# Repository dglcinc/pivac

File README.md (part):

# pivac
Python package to pull data from Raspberry-Pi (RPi)-based inputs, and output JSON data. Supports the assembly and delivery of RPi-based monitoring and control solutions, like HVAC and home automation. Could also be used for other monitoring projects like home brewing and sous vide. These inputs include both RPi hardware inputs (like GPIO pins and GPIO-supported protocols like 1-Wire), as well as external sources useful for assembling a complete solution, such as HTTP-based data feeds and web sites (a.k.a. screen scraping.) This package is "input-only" - no provision is (currently) made to process updates.

Currently supported inputs include:

* **1-WireTherm**: 1-Wire-based Dallas temperature sensors (thermometers)
* **GPIO**: Generic reads of RPi GPIO pins, pulled high or low using internal pullup resistors
* **RedLink**: Screen scraping of Honeywell's website for RedLink thermostats, mytotalconnectcomfort.com (requires an account and installed RedLink equipment)
* **TED5000**: Parsing of the live XML feed from the TED5000 home energy monitoring solution
* **ArduinoSensor**: Pressure sensor data from an Arduino over HTTP (e.g. Fusch 100PSI, Fusch 200PSI) — a single implementation used by multiple config sections via the `module:` key
* **Emporia**: Per-circuit power readings in Watts from an Emporia Vue Gen 2 energy monitor, via the PyEmVue cloud API
* **Sentry**: Boiler operating data from an NTI Trinity Ti-200 boiler controller, read via computer vision from a Tapo C120 IP camera pointed at the Sentry 2100 display
* **FlirFX**: Temperature and humidity from a FLIR camera

The package is extensible, so if the supported inputs don't meet your needs, you can add your own.

The package provides each input individually, so you can pick and choose which ones you want. Customization is possible via a configuration file.

# Overview
This package has the modest aspiration of simplifying a certain class of monitoring (and eventually control) use cases for Raspberry Pi based projects, by providing pre-built recipes for acquiring data, and emitting the data in JSON format. It has no aspirations to replace more general RPi packages like GPIO and w1Therm (in fact it is built on top of them). Examples cases using JSON data:

* Delivering a status website on your RPi, available on your local network
* Modeling your RPi as an Amazon Web Services (AWS) IOT "thing", uploading your data as thing shadow "updates", and using AWS Lambdas to do stuff (store data, render static websites, etc.)
* Inputting data to a [Signal K](http://www.signalk.org) server running on your RPi, and leveraging the Signal K ecosystem to process and display your data
* Capturing a time series collection of the data in a database such as InfluxDB, and analyzing in a charting tool such as Grafana

## Standard call interface, Diverse inputs, JSON output
The core concept of this package is simple - go get some data from somewhere related to your use case (a piece of HVAC equipment or a home automation product website) and return it as a JSON-formatted data collection. You can then reformat it and deliver it in a number of different ways. A standard call interface and configuration file format makes it easy to add new modules for new input types.

## Why Python?
What can I say, I like Python. It's easy and fun to write some pretty fancy stuff. And supposedly it's [where the Pi in Raspberry Pi comes from](https://www.techspot.com/article/531-eben-upton-interview/) (Pi-thon, get it?).

## Why RPi and not Arduino
I actually started this project on Arduino, using a packaged Arduino-based PLC from [Digital Loggers](https://dlidirect.com/products/diy-programmable-controller). There are some advantages to using the Arduino in terms of analog inputs, PWM handling, performance, etc. and the DL PLC is pretty cool, with optical input isolators, open collector outputs, LCD screen, etc. I didn't really need these features, and the programming model was not fun (e.g. coding Lua on NodeMCU to do your Wi-Fi comms., serial-loading sketches constantly, etc.) Great if you need it, a pain if you don't. I abandoned this because the RPi is way simpler - I can SSH in headless, use a standard UNIX programming model and tools (which I know very well) code in fun languages like Python -- what's not to like? The code for the (archived) Arduino version is at [HVAC-plc](https://github.com/dglcinc/HVAC-plc).

Ambitious contributors/forkers who like the RPi model and also have more need for Arduino features could follow the suggestion in this [excellent Maker article](http://makezine.com/projects/tutorial-raspberry-pi-gpio-pins-and-python/) to piggy-back an Arduino to your RPi's serial port, and add a module that reads the Arduino and supplies JSON as output.

## Why polling of the GPIO pins, rather than events?
* It's simpler
* I want to store time series data without interpolating
* It makes it easy to disconnect and reconnect to your aggregator and still see the complete picture of current state

I suppose you could do some work to optimize by only generating output when state changes, but that gets a lot more complicated and I don't really see the benefit for my use case, so I didn't do it.

## Why not control too, not just monitoring?
Eventually. For the HVAC use case specifically, I have shied away from making the correct operation of the HVAC system dependent on the RPi:

* It means you can't condition your space if you have a problem with the RPi
* It's very hard to find HVAC technicians that can or will work on RPi-based controls

I'm pondering a design that allows some control or automation by the RPi, but fallback to full mechanical behavior if the RPi is down. When I have a good plan for that I'll reconsider having the RPi control the system.

## Suggestions for Processing the Output
My original project delivered the JSON from my data sources into a python script that dynamically generated a simple web page on the RPi as an Apache-based Python CGI. I then internet-enabled my project (to avoid doing port forwarding to my RPi, and to learn AWS IOT...) by setting up the RPi as a thing on Amazon's IOT service, and using a Lambda to generate an S3-based static page whenever the thing shadow is updated by my RPi, once every few seconds. I know kinda sloppy but it works... You could optimize your updating to minimize charges for Lambda, etc., but at the volume I consume (low and cheap) it's not a priority. The github repository for the archived version is at [HVAC-pi](https://github.com/dglcinc/HVAC-pi), including the python cgi in the /local subdirectory, and the AWS thing code in /hvac-pi-aws.

## Signal K!
I serendipitously stumbled on a project targeted at the boating community, [Signal K](http://www.signalk.org). Some features of that project are strikingly similar to mine (gather data from a variety of disparate sources and protocols and rationalize them into a JSON-based data stream). They have more and better developers, and a pretty highly evolved ecosystem. So I've converted to outputting my JSON to a Signal K server, and then using the tools in that ecosystem (such as the excellent iOS app [WilhelmSK](http://www.wilhelmsk.com)) to store and render my data. It's very cool. Check it out. Here are screenshots from the WilhelmSK iPhone and iPad app. The first screen is the real-time gauges to monitor all my vital statistics, and the second screen is a Grafana dashboard visualizing time series data for all the inputs, stored in an InfluxDB database.

# Architecture
The features of the architecture are:

* **Isolated Operation**: Doesn't impact operation of the HVAC equipment (no direct control, to avoid HVAC downtime due to RPI and sensor issues)
* **Real Time and Historical Data**: Displays status of all the equipment, stores and plots historical data automatically for all modules
* **Modular Sensor Inputs**: Modular sensor feeds so it can be adapted to different systems with minimal coding
* **User-Configurable Display**: Easily configurable user interface for personal preferences, mobile display works on-premise or remote

The data flow and component view of the architecture is as follows:

```mermaid
%%{init: {'flowchart': {'htmlLabels': true, 'curve': 'linear', 'subgraphTitleMargin': {'top': 30, 'bottom': 30}}, 'theme': 'base'}}%%
graph TD
    subgraph Devices["Physical Devices"]
        A1["Arduino<br/>10.0.0.114<br/>Hydronic PSI<br/>(Fusch 100 PSI)"]
        A2["Arduino<br/>10.0.0.219<br/>DHW PSI<br/>(Fusch 200 PSI)"]
        CAM["Tapo C120<br/>10.0.0.19<br/>RTSP 2560×1440"]
        OW["1-Wire Sensors<br/>GPIO (temp)"]
        GPIO["GPIO Pins<br/>Switches / Relays"]
        RL["Honeywell<br/>mytotalconnectcomfort.com<br/>(HTTPS)"]
        TED["TED5000<br/>10.0.0.49<br/>⚠ disabled"]
        FLIR["FLIR FX Camera<br/>⚠ disabled"]
    end

    subgraph Pivac["pivac"]
        NOTE["📝 Python | ~/github/pivac<br/>systemd services"]
        P1["pivac.ArduinoPSI<br/>pivac-arduino-psi.service"]
        P2["pivac.ArduinoThermPSI<br/>pivac-arduino-therm-psi.service"]
        P3["pivac.Sentry<br/>pivac-sentry.service<br/>(OpenCV perspective warp<br/>+ 7-seg digit recognition)"]
        P4["pivac.OneWireTherm<br/>pivac-1wire.service"]
        P5["pivac.GPIO<br/>pivac-gpio.service"]
        P6["pivac.RedLink<br/>pivac-redlink.service<br/>(screen scraping)"]
        PROV["pivac-provider.py<br/>(WebSocket delta push<br/>+ JWT auth)"]
    end

    subgraph RPi["Raspberry Pi 4 (4GB, Debian 13 aarch64)"]
        SK["SignalK v2.22.1<br/>:3000"]
        INFLUX["InfluxDB 2.7.10<br/>:8086"]
    end

    subgraph Visualization["Visualization"]
        GRAFANA["Grafana 11.2.2<br/>30s refresh<br/>:3001"]
        WILHELM["WilhelmSK<br/>(iPad / iPhone)"]
    end

    %% Device → Module connections
    A1 -->|TCP/serial| P1
    A2 -->|TCP/serial| P2
    CAM -->|RTSP stream| P3
    OW -->|GPIO| P4
    GPIO -->|GPIO| P5
    RL -->|HTTPS scrape| P6

    %% Modules → provider
    P1 & P2 & P3 & P4 & P5 & P6 --> PROV

    %% Provider → SignalK
    PROV -->|WebSocket delta<br/>hvac.boiler.sentry.*<br/>hvac.*.temp, psi, etc.| SK

    %% SignalK → storage
    SK -->|InfluxDB plugin| INFLUX

    %% Visualization
    INFLUX --> GRAFANA
    SK -->|WebSocket| WILHELM

    %% Styling
    classDef disabled fill:#eee,stroke:#999,color:#999
    classDef device fill:#dbeafe,stroke:#3b82f6
    classDef module fill:#dcfce7,stroke:#22c55e
    classDef infra fill:#fef9c3,stroke:#eab308
    classDef viz fill:#fce7f3,stroke:#ec4899

    class TED,FLIR disabled
    class A1,A2,CAM,OW,GPIO,RL device
    class P1,P2,P3,P4,P5,P6,PROV module
    class SK,INFLUX,RPi infra
    class GRAFANA,WILHELM viz
    
    style NOTE fill:#fffacd,stroke:#999,color:#333
```

# Installing the Package

Clone the repository and install into a Python virtual environment:

```bash
git clone https://github.com/dglcinc/pivac
cd pivac
python3 -m venv ~/pivac-venv
source ~/pivac-venv/bin/activate
pip install -e .
```

If you need the RPi-specific hardware dependencies (GPIO, 1-wire), also run:
```bash
pip install RPi.GPIO w1thermsensor --break-system-packages
```

If you prefer not to install at all, the scripts and config will work properly using the local repository directory as the launch point — just run `python scripts/pivac-provider.py` directly from the clone.

## Configuring the Package
Copy the sample config and edit it for your setup:

```bash
sudo mkdir -p /etc/pivac
sudo cp config/config.yml.sample /etc/pivac/config.yml
sudo nano /etc/pivac/config.yml
```

Each top-level key in the config file (starting with `pivac.`) is a provider instance name. By default, it is also the Python module that gets loaded. If you want multiple instances of the same module (e.g. two sensors of the same type with different IPs), add a `module:` key to point to the shared implementation:

```yaml
pivac.Sensor1:
    module: pivac.ArduinoSensor
    ipaddr: 10.0.0.10
    ...

pivac.Sensor2:
    module: pivac.ArduinoSensor
    ipaddr: 10.0.0.11
    ...
```

Enable or disable modules by setting `enabled: true/false`. A complete, commented sample is provided as `config/config.yml.sample`.

**Signal K integration** requires a `pivac_config:` section in your config file containing the SignalK host, port, and credentials:

```yaml
pivac_config:
    signalk:
        host: localhost
        port: 3000
        username: admin
        password: yourpassword
```

Note: `pivac_config` is a reserved key for framework settings — it is not treated as a provider module.

# Using the Package

## The Scripts

* **`pivac-provider.py`** — the main script. It dynamically loads modules from your config file and either pushes data to Signal K via WebSocket (daemon mode) or outputs JSON to stdout (useful for testing). The `--help` option provides full documentation; arguments and choices are dynamically configured from the contents of the config file.
* **`pivac-provider.sh`** — a wrapper for the .py script that restarts it if it fails (e.g. when running with `--daemon`). This script execs to `provider.sh` and inherits its behavior.
* **`provider.sh`** — a generic wrapper script that restarts a script if it fails and catches the SIGHUP signal (`kill -1`) to restart the script. A standard kill (SIGINT) will stop both the wrapper and the script.

```bash
# Test a module - outputs JSON to stdout
python scripts/pivac-provider.py pivac.GPIO

# Pretty-print output for debugging
python scripts/pivac-provider.py pivac.OneWireTherm --format pretty

# Run continuously (daemon mode) - connects to Signal K via WebSocket
python scripts/pivac-provider.py pivac.RedLink --daemon

# Options
#   --loglevel DEBUG|INFO|WARNING|ERROR|CRITICAL
#   --format compact|pretty
#   --daemon [N]   (run forever, or N iterations)
```

## Process Management

In production, each module runs as a dedicated systemd service. Service files are provided in `scripts/systemd/`. To install:

```bash
sudo cp scripts/systemd/*.service /etc/systemd/system/
sudo systemctl daemon-reload
sudo systemctl enable pivac-1wire pivac-redlink pivac-gpio pivac-arduino-psi pivac-arduino-therm-psi pivac-emporia pivac-sentry
sudo systemctl start pivac-1wire pivac-redlink pivac-gpio pivac-arduino-psi pivac-arduino-therm-psi pivac-emporia pivac-sentry
```

Each service connects independently to Signal K via WebSocket and restarts automatically on failure.

## The Modules
The pivac package currently contains the following modules:

* GPIO
* OneWireTherm
* TED5000
* RedLink
* ArduinoSensor
* Emporia
* Sentry
* FlirFX (disabled by default)

## Adding a New Provider Module

Pivac is designed so that new data providers can be added without modifying any framework code. The steps are:

**1. Write the module**

Create `pivac/MyModule.py`. The module must implement a `status()` function with this signature:

```python
def status(config={}, output="default"):
    ...
```

- When `output="default"`: return a plain Python dict of sensor readings (used for command-line testing)
- When `output="signalk"`: return a Signal K delta dict built using the pivac helper functions:

```python
from pivac import sk_init_deltas, sk_add_source, sk_add_value

deltas = sk_init_deltas()
source = sk_add_source(deltas)
sk_add_value(source, "environment.inside.myreading", value)
return deltas
```

- On error: log a warning and return an empty delta — don't raise an exception, so the service keeps running
- The module name must start with `pivac.` (e.g. `pivac.MyModule`)

You can use the `propagate_defaults()` helper to copy top-level config values down to each entry in `inputs:` — see `GPIO.py` or `OneWireTherm.py` for examples.

**2. Add a config section**

Add a section to `/etc/pivac/config.yml` using the module's full Python name as the key:

```yaml
pivac.MyModule:
    description: My new sensor module
    enabled: true
    daemon_sleep: 5
    # ... module-specific config keys ...
```

If you need multiple independent instances of the same module (e.g. two sensors with different IPs), give each a unique key and use the `module:` key to point them both at the same implementation:

```yaml
pivac.MySensor1:
    module: pivac.MyModule
    ipaddr: 10.0.0.10

pivac.MySensor2:
    module: pivac.MyModule
    ipaddr: 10.0.0.11
```

**3. Test standalone**

Verify the module works before connecting it to Signal K:

```bash
source ~/pivac-venv/bin/activate
python scripts/pivac-provider.py pivac.MyModule --format pretty
```

This outputs the raw JSON to stdout without needing Signal K running.

**4. Create a systemd service file**

Copy an existing service file and adapt it:

```bash
cp scripts/systemd/pivac-gpio.service scripts/systemd/pivac-mymodule.service
```

Edit the new file — change the `Description` and the module name in `ExecStart`:

```ini
[Unit]
Description=Pivac MyModule provider
After=network.target signalk.service
Requires=signalk.service

[Service]
Type=simple
User=pi
Environment=PIVAC_CFG=/etc/pivac/config.yml
ExecStart=/home/pi/pivac-venv/bin/python3 /home/pi/github/pivac/scripts/pivac-provider.py pivac.MyModule --loglevel ERROR --daemon
Restart=always
RestartSec=10

[Install]
WantedBy=multi-user.target
```

**5. Install and start the service**

```bash
sudo cp scripts/systemd/pivac-mymodule.service /etc/systemd/system/
sudo systemctl daemon-reload
sudo systemctl enable pivac-mymodule
sudo systemctl start pivac-mymodule
```

**6. Verify**

```bash
journalctl -u pivac-mymodule -n 50 --no-pager
```

## Initialization
* **`pivac.set_config(configfile="")`**: This method must be called before using any of the modules. It locates and reads the config file, first in `/etc/pivac/config.yml` then in `config/config.yml` relative to the parent directory of the scripts, if you do not specify it. Returns the `config` dictionary. This currently can only be set once, because the data read from the config file is used to load modules by the `pivac-provider.py` script. If you attempt to set again it will return the current config dict.

* **`pivac.get_config()`**: Returns the config dictionary read from the config file.

* **`[module].status(config={}, output="default")`**: Each module implements (at least) this method, and can be used individually in your project. Each module supports one interface method, status(). Status takes two arguments - a dictionary containing the configuration for the module read from the configuration file, and a string indicating the output type (`"default"` for plain JSON dict, `"signalk"` for a Signal K delta structure).

### Configuration of RPi 1-Wire (OneWireTherm)
In order to use the OneWireTherm module, you need to enable the OneWire RPi driver. You can do this in either the GUI system configuration (if you're using the desktop) or on the command line:

```
sudo raspi-config
[select "Interfacing Options"]
[select "1-Wire"]
[select "<Yes>"]
exit
```

## GPIO
* **`GPIO.status(config={}, output="default")`**: each pin included in the configuration file will be reported as "true" if on and "false" if off.
	* For pins configured with pull-down resistors, "on" or "true" means the pin is attached to voltage.
	* The module configuration file provides options for specifying pull-up or pull-down, as well as names to map pins to in the JSON output.
	* For pins configured with pull-up resistors, "on" or "true" means the pin is attached to ground.

Example output using the sample yml file with `python pivac-provider.py pivac.GPIO --format pretty`:

```
{
    "ZV": true,
    "DHW": false,
    "BLR": true,
    "BOS2": false,
    "BOS1": false,
    "DEHUM": false,
    "HPCALL": false
}
```

## OneWireTherm

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
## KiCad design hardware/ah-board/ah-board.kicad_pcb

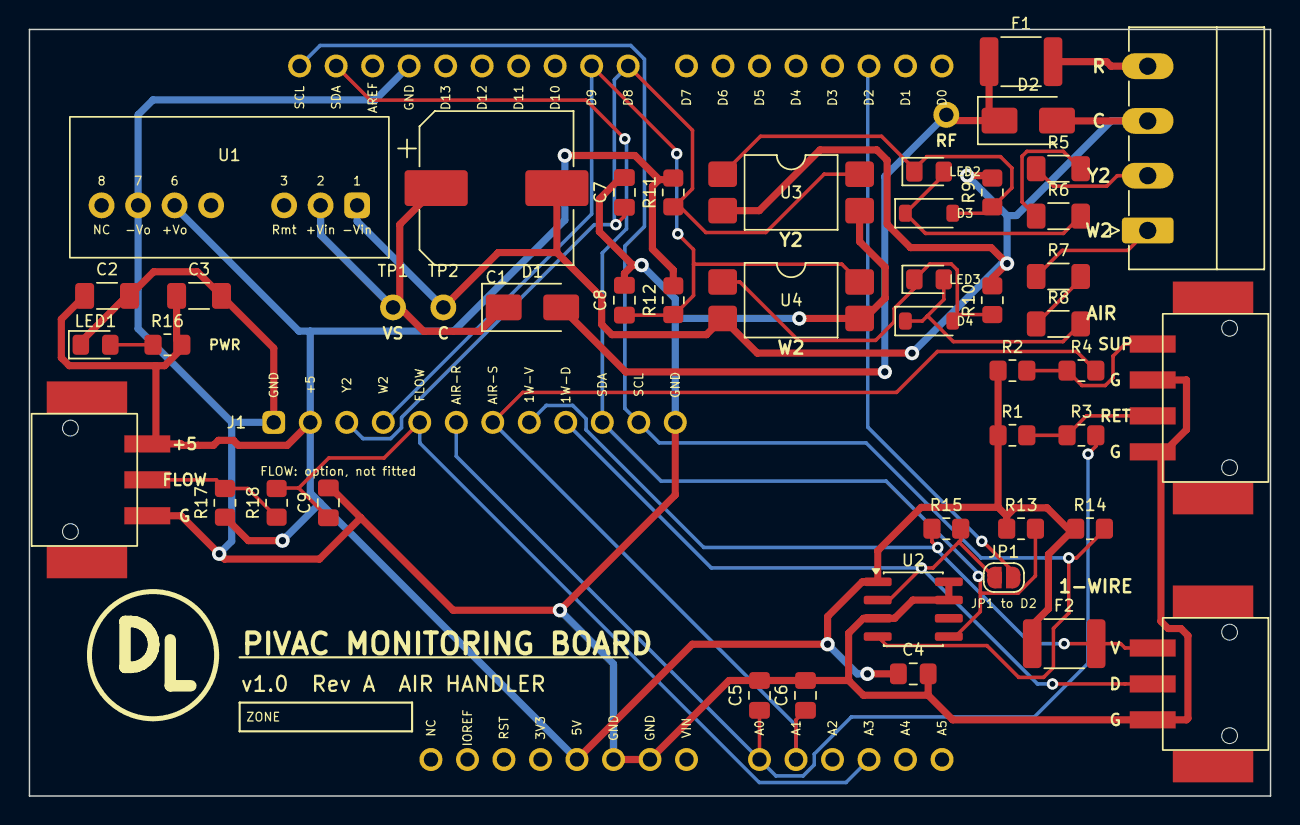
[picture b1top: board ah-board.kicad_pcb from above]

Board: 2 copper layers, 86.4 x 53.3 mm, 53 parts (0 on the bottom side), 28 nets.

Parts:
C1: 100u 63V; CP_Elec_10x10.5
C2: 10u; C_1206_3216Metric_Pad1.33x1.80mm_HandSolder
C3: 22u; C_1206_3216Metric_Pad1.33x1.80mm_HandSolder
C4, C5, C6: 100n; C_0805_2012Metric_Pad1.18x1.45mm_HandSolder
C7, C8: 1u; C_0805_2012Metric_Pad1.18x1.45mm_HandSolder
C9: 1n C0G; C_0805_2012Metric_Pad1.18x1.45mm_HandSolder
D1: S1M; D_SMA
D2: SMAJ43CA; D_SMA
D3, D4: 1N4148W; D_SOD-123
F1, F2: 1812L020/60DR; Fuse_1812_4532Metric_Pad1.30x3.40mm_HandSolder
J1: test row; TestRow_1x12
J10: Arduino header; ArduinoHeader_1x10
J11, J12: Arduino header; ArduinoHeader_1x8
J13: Arduino header; ArduinoHeader_1x6
JP1: DATA->D2; SolderJumper-2_P1.3mm_Open_RoundedPad1.0x1.5mm
LED1: green PWR; LED_0805_2012Metric_Pad1.15x1.40mm_HandSolder
LED2: blue; LED_0805_2012Metric_Pad1.15x1.40mm_HandSolder
LED3: red; LED_0805_2012Metric_Pad1.15x1.40mm_HandSolder
R1, R2: 10k0 0.1%; R_0805_2012Metric_Pad1.20x1.40mm_HandSolder
R3, R4, R9, R10, R16: 1k; R_0805_2012Metric_Pad1.20x1.40mm_HandSolder
R5, R6, R7, R8: 2k2; R_1206_3216Metric_Pad1.30x1.75mm_HandSolder
R11, R12, R17: 10k; R_0805_2012Metric_Pad1.20x1.40mm_HandSolder
R13, R14, R15: 4k7; R_0805_2012Metric_Pad1.20x1.40mm_HandSolder
R18: 100R; R_0805_2012Metric_Pad1.20x1.40mm_HandSolder
TB1: MC 1,5/4-G-3,81 24VAC; PhoenixContact_MC_1,5_4-G-3.81_1x04_P3.81mm_Horizontal
TB2: PTSM 0,5/4-HH-2,5-SMD air; PTSM_0.5_4-HH-2.5-SMD
TB3: PTSM 0,5/3-HH-2,5-SMD 1-wire; PTSM_0.5_3-HH-2.5-SMD
TB4: PTSM 0,5/3-HH-2,5-SMD flow; PTSM_0.5_3-HH-2.5-SMD
TP1: VS; TestLoop
TP2: C; TestLoop
TP3: RF; TestLoop
U1: TMR 3-4811WI; TMR3WI_TMR12WI_SIP-8
U2: DS2482S-100+; SOIC-8_3.9x4.9mm_P1.27mm
U3, U4: LTV-814S; SMDIP-4_W9.53mm

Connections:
+5V: C2.1, C3.1, C4.1, F2.1, J1.2, J12.5, R1.1, R2.1, R11.2, R12.2, R13.1, R14.1, R16.2, R17.1, TB4.3, U1.6, U2.1
A0: C5.1, J1.6, J13.1, R3.2
A1: C6.1, J1.7, J13.2, R4.2
A3: C9.1, J1.5, J13.4, R18.2
ACF: D1.2, D2.1, F1.1, TP3.1
ACR: F1.2, TB1.4
AIRR: R1.2, R3.1, TB2.3
AIRS: R2.2, R4.1, TB2.1
COM: C1.2, D2.2, R9.2, R10.2, TB1.3, TP2.1, U1.1, U3.2, U4.2
D2: J11.6, JP1.2
D8: C7.1, J1.3, J10.10, R11.1, U3.4
D9: C8.1, J1.4, J10.9, R12.1, U4.4
FLOW: R17.2, R18.1, TB4.2
GND: C2.2, C3.2, C4.2, C5.2, C6.2, C7.2, C8.2, C9.2, J1.1, J1.12, J10.4, J12.6, J12.7, LED1.1, TB2.2, TB2.4, TB3.3, TB4.1, U1.7, U2.3, U2.7, U2.8, U3.3, U4.3
OWD: J1.9, JP1.1, R15.2, TB3.2, U2.2
OWV: F2.2, J1.8, R15.1, TB3.1
PWRLED: LED1.2, R16.1
SCL: J1.11, J10.1, R14.2, U2.4
SDA: J1.10, J10.2, R13.2, U2.5
VS: C1.1, D1.1, TP1.1, U1.2
W2: R7.1, TB1.1
W2A: R7.2, R8.1
W2B: D4.1, LED3.2, R8.2
W2C: D4.2, LED3.1, R10.1, U4.1
Y2: R5.1, TB1.2
Y2A: R5.2, R6.1
Y2B: D3.1, LED2.2, R6.2
Y2C: D3.2, LED2.1, R9.1, U3.1

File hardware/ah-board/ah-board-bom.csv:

qty,value,footprint,references,fitted
1,100u 63V,CP_Elec_10x10.5,C1,yes
1,10u,C_1206_3216Metric_Pad1.33x1.80mm_HandSolder,C2,yes
1,22u,C_1206_3216Metric_Pad1.33x1.80mm_HandSolder,C3,yes
3,100n,C_0805_2012Metric_Pad1.18x1.45mm_HandSolder,C4 C5 C6,yes
2,1u,C_0805_2012Metric_Pad1.18x1.45mm_HandSolder,C7 C8,yes
1,1n C0G,C_0805_2012Metric_Pad1.18x1.45mm_HandSolder,C9,no
1,S1M,D_SMA,D1,yes
1,SMAJ43CA,D_SMA,D2,yes
2,1N4148W,D_SOD-123,D3 D4,yes
2,1812L020/60DR,Fuse_1812_4532Metric_Pad1.30x3.40mm_HandSolder,F1 F2,yes
1,test row,TestRow_1x12,J1,yes
1,DATA->D2,SolderJumper-2_P1.3mm_Open_RoundedPad1.0x1.5mm,JP1,yes
1,Arduino header,ArduinoHeader_1x10,J10,yes
2,Arduino header,ArduinoHeader_1x8,J11 J12,yes
1,Arduino header,ArduinoHeader_1x6,J13,yes
1,green PWR,LED_0805_2012Metric_Pad1.15x1.40mm_HandSolder,LED1,yes
1,blue,LED_0805_2012Metric_Pad1.15x1.40mm_HandSolder,LED2,yes
1,red,LED_0805_2012Metric_Pad1.15x1.40mm_HandSolder,LED3,yes
2,10k0 0.1%,R_0805_2012Metric_Pad1.20x1.40mm_HandSolder,R1 R2,yes
5,1k,R_0805_2012Metric_Pad1.20x1.40mm_HandSolder,R3 R4 R9 R10 R16,yes
4,2k2,R_1206_3216Metric_Pad1.30x1.75mm_HandSolder,R5 R6 R7 R8,yes
2,10k,R_0805_2012Metric_Pad1.20x1.40mm_HandSolder,R11 R12,yes
2,4k7,R_0805_2012Metric_Pad1.20x1.40mm_HandSolder,R13 R14,yes
1,4k7,R_0805_2012Metric_Pad1.20x1.40mm_HandSolder,R15,no
1,10k,R_0805_2012Metric_Pad1.20x1.40mm_HandSolder,R17,no
1,100R,R_0805_2012Metric_Pad1.20x1.40mm_HandSolder,R18,no
1,"MC 1,5/4-G-3,81 24VAC","PhoenixContact_MC_1,5_4-G-3.81_1x04_P3.81mm_Horizontal",TB1,yes
1,"PTSM 0,5/4-HH-2,5-SMD air",PTSM_0.5_4-HH-2.5-SMD,TB2,yes
1,"PTSM 0,5/3-HH-2,5-SMD 1-wire",PTSM_0.5_3-HH-2.5-SMD,TB3,yes
1,"PTSM 0,5/3-HH-2,5-SMD flow",PTSM_0.5_3-HH-2.5-SMD,TB4,no
1,TMR 3-4811WI,TMR3WI_TMR12WI_SIP-8,U1,yes
1,DS2482S-100+,SOIC-8_3.9x4.9mm_P1.27mm,U2,yes
2,LTV-814S,SMDIP-4_W9.53mm,U3 U4,yes

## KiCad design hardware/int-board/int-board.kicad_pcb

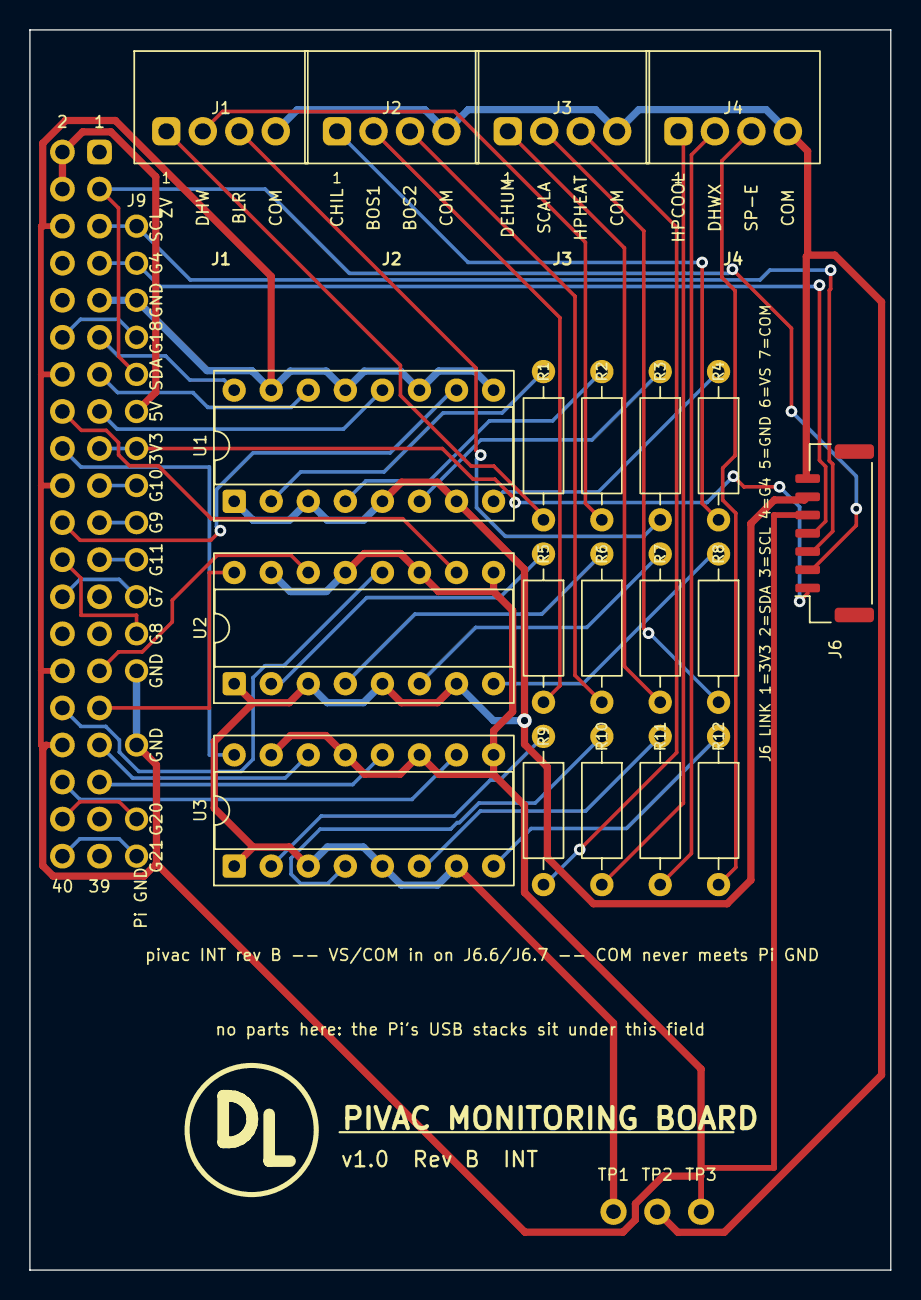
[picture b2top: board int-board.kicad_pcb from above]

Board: 2 copper layers, 59.0 x 85.0 mm, 25 parts (1 on the bottom side), 52 nets.

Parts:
J1, J2, J3, J4: PTSM 0,5/4-HH-2,5-THR; PTSM_0.5_4-HH-2.5-THR
J5: Pi 40-pin socket; PiHeader_2x20_Socket_Bottom
J6: GH SM07B link to EXT; JST_GH_SM07B-GHS-TB_1x07-1MP_P1.25mm_Horizontal
J9: GPIO breakout; Shadow_1x20
R1, R2, R3, R4, R5, R6, R7, R8, R9, R10, R11, R12: 10k 1/4W; R_Axial_DIN0207_L6.3mm_D2.5mm_P10.16mm_Horizontal
TP1: VS; TestPad
TP2: COM; TestPad
TP3: GND; TestPad
U1, U2, U3: LTV-847; DIP-16_W7.62mm_Socket

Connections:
3V3: J5.17, J6.1, J9.9
+5V: J5.2, J5.4, J9.8
COM: J1.4, J2.4, J3.4, J4.4, J6.7, TP2.1
GND: J5.6, J5.9, J5.14, J5.20, J5.30, J5.34, J6.5, J9.5, J9.15, J9.17, TP3.1, U1.9, U1.11, U1.13, U1.15, U2.9, U2.11, U2.13, U2.15, U3.9, U3.11, U3.13, U3.15
GPIO4: J5.7, J6.4, J9.4
GPIO5: J5.29, U2.14
GPIO6: J5.31, U2.16
GPIO7: J5.26, J9.13
GPIO8: J5.24, J9.14
GPIO9: J5.21, J9.11
GPIO10: J5.19, J9.10
GPIO11: J5.23, J9.12
GPIO12: J5.32, U2.12
GPIO13: J5.33, U3.14
GPIO16: J5.36, U3.10
GPIO17: J5.11, U1.16
GPIO18: J5.12, J9.6
GPIO19: J5.35, U3.12
GPIO20: J5.38, J9.19
GPIO21: J5.40, J9.20
GPIO22: J5.15, U1.12
GPIO23: J5.16, U2.10
GPIO24: J5.18, U3.16
GPIO25: J5.22, U1.10
GPIO27: J5.13, U1.14
K1: R1.1, U1.2
K2: R2.1, U1.4
K3: R3.1, U1.6
K4: R4.1, U1.8
K5: R5.1, U2.2
K6: R6.1, U2.4
K7: R7.1, U2.6
K8: R8.1, U2.8
K9: R9.1, U3.2
K10: R10.1, U3.4
K11: R11.1, U3.6
K12: R12.1, U3.8
SCL: J5.5, J6.3, J9.3
SDA: J5.3, J6.2, J9.7
S_BLR: J1.3, R3.2
S_BOS1: J2.2, R5.2
S_BOS2: J2.3, R6.2
S_CHIL: J2.1, R4.2
S_DEHUM: J3.1, R7.2
S_DHW: J1.2, R2.2
S_DHWX: J4.2, R11.2
S_HPCOOL: J4.1, R10.2
S_HPHEAT: J3.3, R9.2
S_SCALA: J3.2, R8.2
S_SP-E: J4.3, R12.2
S_ZV: J1.1, R1.2
VS: J6.6, TP1.1, U1.1, U1.3, U1.5, U1.7, U2.1, U2.3, U2.5, U2.7, U3.1, U3.3, U3.5, U3.7

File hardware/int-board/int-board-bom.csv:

qty,value,footprint,references,fitted
4,"PTSM 0,5/4-HH-2,5-THR",PTSM_0.5_4-HH-2.5-THR,J1 J2 J3 J4,yes
1,Pi 40-pin socket,PiHeader_2x20_Socket_Bottom,J5,yes
1,GH SM07B link to EXT,JST_GH_SM07B-GHS-TB_1x07-1MP_P1.25mm_Horizontal,J6,yes
1,GPIO breakout,Shadow_1x20,J9,yes
12,10k 1/4W,R_Axial_DIN0207_L6.3mm_D2.5mm_P10.16mm_Horizontal,R1 R2 R3 R4 R5 R6 R7 R8 R9 R10 R11 R12,yes
3,LTV-847,DIP-16_W7.62mm_Socket,U1 U2 U3,yes

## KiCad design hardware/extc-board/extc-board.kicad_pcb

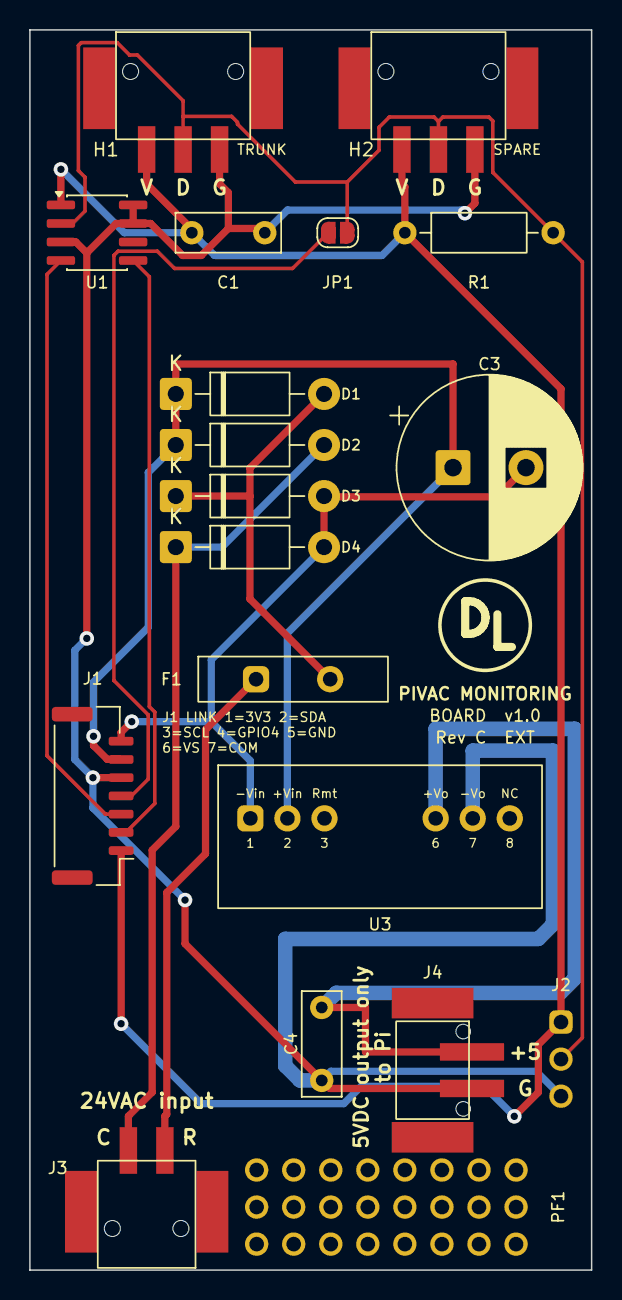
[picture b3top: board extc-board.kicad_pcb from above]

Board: 2 copper layers, 38.5 x 85.0 mm, 19 parts (0 on the bottom side), 12 nets.

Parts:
C1: 100n; C_Rect_L7.0mm_W2.5mm_P5.00mm
C3: 470u 63V; CP_Radial_D12.5mm_P5.00mm
C4: 1u; C_Rect_L7.0mm_W2.5mm_P5.00mm
D1, D2, D3, D4: 1N4007; D_DO-41_SOD81_P10.16mm_Horizontal
F1: PTC 1.1A 60V; PTC_Radial_P5.08_Standing
H1, H2: PTSM 0,5/3-HH-2,5-SMD; PTSM_0.5_3-HH-2.5-SMD
J1: GH BM07B link to INT; JST_GH_BM07B-GHS-TBT_1x07-1MP_P1.25mm_Vertical
J2: VCC DATA GND; Pads_1x3
J3: PTSM 0,5/2-HH-2,5-SMD 24 VAC; PTSM_0.5_2-HH-2.5-SMD
J4: PTSM 0,5/2-HV-2,5-SMD 5V OUT; PTSM_0.5_2-HV-2.5-SMD
JP1: GPIO4->DATA; SolderJumper-2_P1.3mm_Open_RoundedPad1.0x1.5mm
PF1: proto; Proto_8x3
R1: 2k2 rollback; R_Axial_DIN0207_L6.3mm_D2.5mm_P10.16mm_Horizontal
U1: DS2482-100; SOIC-8_3.9x4.9mm_P1.27mm
U3: TMR 12-4811WI; TMR12WI_SIP-8

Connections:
+5V: C4.1, J4.1, U3.6
ACC: D2.2, D4.1, J3.2
ACF: D1.2, D3.1, F1.2
ACR: F1.1, J3.1
COM: C3.2, D3.2, D4.2, J1.7, U3.1
DATA: H1.2, H2.2, J2.2, JP1.2, R1.2, U1.2
GND: C1.2, C4.2, H1.3, H2.3, J1.5, J2.3, J4.2, U1.3, U1.7, U1.8, U3.7
GPIO4: J1.4, JP1.1
SCL: J1.3, U1.4
SDA: J1.2, U1.5
VCC: C1.1, H1.1, H2.1, J1.1, J2.1, R1.1, U1.1
VS: C3.1, D1.1, D2.1, J1.6, U3.2

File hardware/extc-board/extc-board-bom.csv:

qty,value,footprint,references,fitted
1,100n,C_Rect_L7.0mm_W2.5mm_P5.00mm,C1,yes
1,470u 63V,CP_Radial_D12.5mm_P5.00mm,C3,yes
1,1u,C_Rect_L7.0mm_W2.5mm_P5.00mm,C4,yes
4,1N4007,D_DO-41_SOD81_P10.16mm_Horizontal,D1 D2 D3 D4,yes
1,PTC 1.1A 60V,PTC_Radial_P5.08_Standing,F1,yes
2,"PTSM 0,5/3-HH-2,5-SMD",PTSM_0.5_3-HH-2.5-SMD,H1 H2,yes
1,GH BM07B link to INT,JST_GH_BM07B-GHS-TBT_1x07-1MP_P1.25mm_Vertical,J1,yes
1,GPIO4->DATA,SolderJumper-2_P1.3mm_Open_RoundedPad1.0x1.5mm,JP1,yes
1,VCC DATA GND,Pads_1x3,J2,yes
1,"PTSM 0,5/2-HH-2,5-SMD 24 VAC",PTSM_0.5_2-HH-2.5-SMD,J3,yes
1,"PTSM 0,5/2-HV-2,5-SMD 5V OUT",PTSM_0.5_2-HV-2.5-SMD,J4,yes
1,2k2 rollback,R_Axial_DIN0207_L6.3mm_D2.5mm_P10.16mm_Horizontal,R1,no
1,DS2482-100,SOIC-8_3.9x4.9mm_P1.27mm,U1,yes
1,TMR 12-4811WI,TMR12WI_SIP-8,U3,yes

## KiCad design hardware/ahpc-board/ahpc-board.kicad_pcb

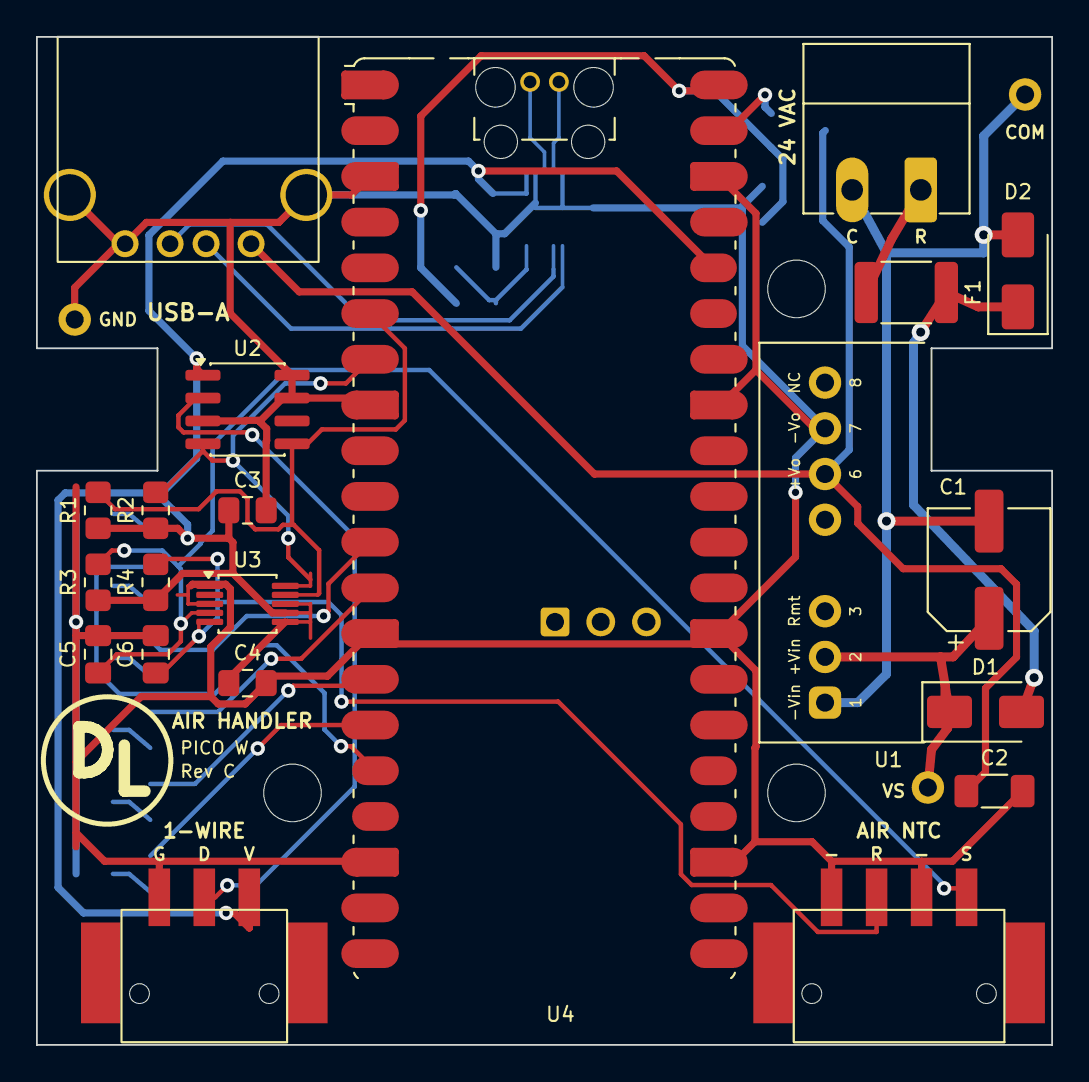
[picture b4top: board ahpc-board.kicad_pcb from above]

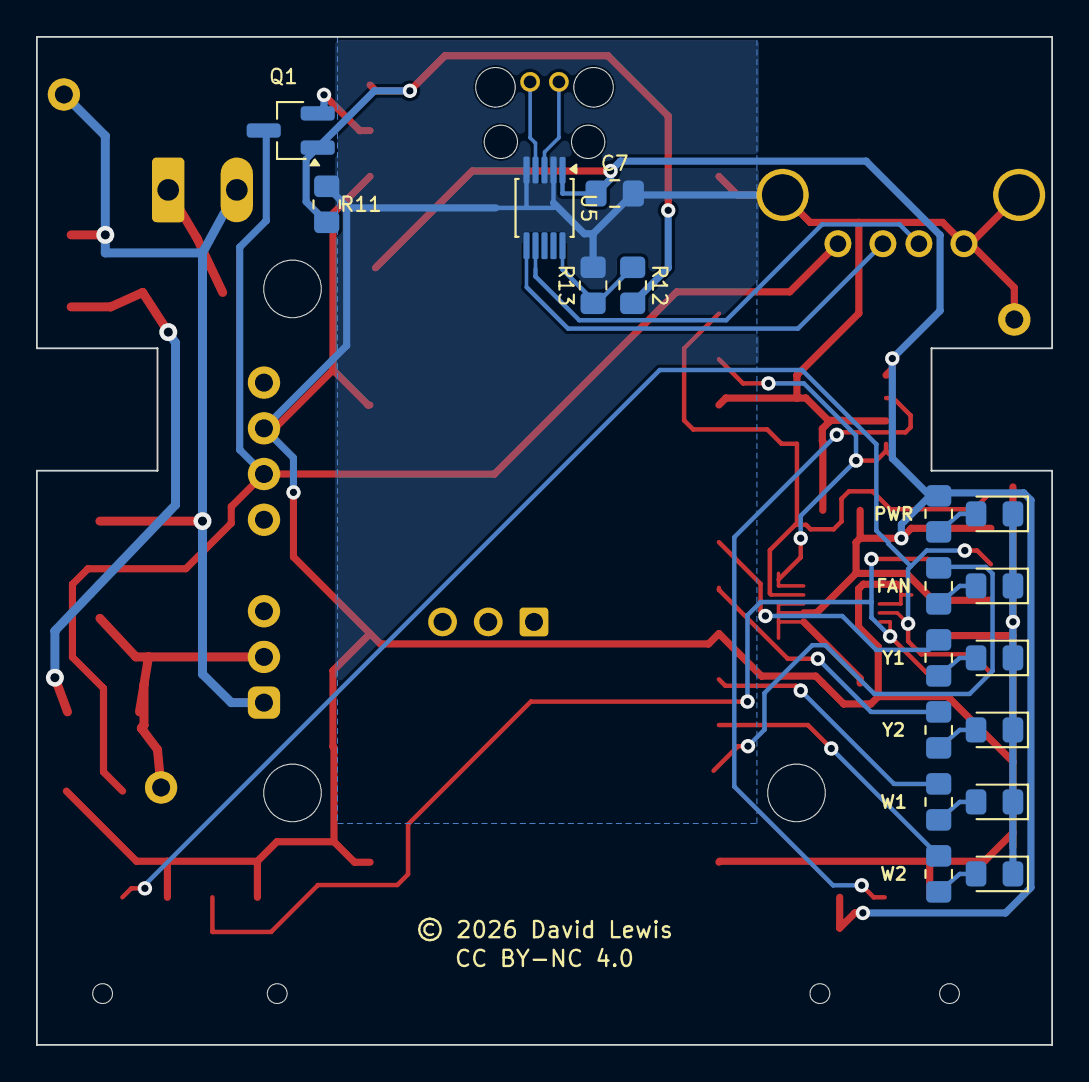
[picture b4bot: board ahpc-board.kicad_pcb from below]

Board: 2 copper layers, 56.4 x 56.0 mm, 45 parts (18 on the bottom side), 30 nets.

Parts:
C1: 47u 50V; CP_Elec_6.3x7.7
C2: 10u; C_1206_3216Metric_Pad1.33x1.80mm_HandSolder
C3, C4, C5, C6, C7: 100n; C_0805_2012Metric_Pad1.18x1.45mm_HandSolder
D1: S1M; D_SMA
D2: SMAJ43CA; D_SMA
F1: PTC 0.2A; Fuse_1812_4532Metric_Pad1.30x3.40mm_HandSolder
H1, H2, H3: #4 x 1/4; MH_4
J1: 3.81 mm 2-pin 24VAC; PhoenixContact_MC_1,5_2-G-3.81_1x02_P3.81mm_Horizontal
J2: PTSM 0,5/3-HH-2,5-SMD; PTSM_0.5_3-HH-2.5-SMD
J3: PTSM 0,5/4-HH-2,5-SMD; PTSM_0.5_4-HH-2.5-SMD
J4: 61400416021; USB_A_61400416021
LED1: 0805 green; LED_0805_2012Metric_Pad1.15x1.40mm_HandSolder
LED2: 0805 yellow; LED_0805_2012Metric_Pad1.15x1.40mm_HandSolder
LED3, LED4: 0805 blue; LED_0805_2012Metric_Pad1.15x1.40mm_HandSolder
LED5, LED6: 0805 red; LED_0805_2012Metric_Pad1.15x1.40mm_HandSolder
Q1: DMG2305UX-7; SOT-23_Handsoldering
R1, R2: 4k7; R_0805_2012Metric_Pad1.20x1.40mm_HandSolder
R3, R4: 10k0 0.1%; R_0805_2012Metric_Pad1.20x1.40mm_HandSolder
R5, R6, R7, R8, R9, R10: 220R; R_0805_2012Metric_Pad1.20x1.40mm_HandSolder
R11: 100k; R_0805_2012Metric_Pad1.20x1.40mm_HandSolder
R12: 22k; R_0805_2012Metric_Pad1.20x1.40mm_HandSolder
R13: 33k; R_0805_2012Metric_Pad1.20x1.40mm_HandSolder
TP1: VS; TestLoop
TP2: COM; TestLoop
TP3: GND; TestLoop
U1: TMR 3-4811WI; TMR3WI_TMR12WI_SIP-8
U2: DS2482S-100+; SOIC-8_3.9x4.9mm_P1.27mm
U3: ADS1115IDGS; MSOP-10_3x3mm_P0.5mm
U4: Pico W SC0918; RaspberryPi_Pico_W_SMD_HandSolder
U5: FSUSB42MUX; MSOP-10_3x3mm_P0.5mm

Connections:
3V3: C3.1, C4.1, C7.1, J2.1, R1.1, R2.1, R3.1, R4.1, R5.2, U2.1, U3.6, U3.7, U3.8, U4.36, U5.1
+5V: C2.1, J4.1, Q1.3, U1.6
ACF: D1.2, D2.1, F1.2
ACR: F1.1, J1.1
A_LED1: LED1.2, R5.1
A_LED2: LED2.2, R6.1
A_LED3: LED3.2, R7.1
A_LED4: LED4.2, R8.1
A_LED5: LED5.2, R9.1
A_LED6: LED6.2, R10.1
COM: C1.2, D2.2, J1.2, TP2.1, U1.1
D+: J4.3, U5.7
D-: J4.2, U5.6
GND: C2.2, C3.2, C4.2, C5.2, C6.2, C7.2, J2.3, J3.2, J3.4, J4.4, J4.S, LED1.1, LED2.1, LED3.1, LED4.1, LED5.1, LED6.1, R11.2, R13.2, TP3.1, U1.7, U2.3, U2.7, U2.8, U3.1, U3.3, U4.3, U4.8, U4.13, U4.18, U4.23, U4.28, U4.33, U4.38, U5.2, U5.5
L_FAN: R6.2, U4.16
L_W1: R9.2, U4.14
L_W2: R10.2, U4.15
L_Y1: R7.2, U4.11
L_Y2: R8.2, U4.12
OE: R12.2, R13.1, U5.10
OW: J2.2, U2.2
PD+: U4.TP3, U5.3
PD-: U4.TP2, U5.4
RET: C6.1, J3.3, R4.2, U3.5
SCL: R2.2, U2.4, U3.10, U4.7
SDA: R1.2, U2.5, U3.9, U4.6
SUP: C5.1, J3.1, R3.2, U3.4
VBUS: Q1.1, R11.1, R12.1, U4.40
VS: C1.1, D1.1, TP1.1, U1.2
VSYS: Q1.2, U4.39

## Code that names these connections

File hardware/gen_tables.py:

# SPDX-License-Identifier: PolyForm-Noncommercial-1.0.0
# Copyright David Lewis
"""Pin and net tables shared by gen-boards.py (placement, nets) and gen-schematics.py."""
PITCH = 2.54

# Channel table: name, plug.position, LTV-847 IC/channel, Pi header pin, BCM
CHANNELS = [
    ("ZV", "J1", 1, 17, 11), ("DHW", "J1", 2, 27, 13), ("BLR", "J1", 3, 22, 15),
    ("CHIL", "J2", 1, 25, 22), ("BOS1", "J2", 2, 6, 31), ("BOS2", "J2", 3, 5, 29),
    ("DEHUM", "J3", 1, 12, 32), ("SCALA", "J3", 2, 23, 16), ("HPHEAT", "J3", 3, 24, 18),
    ("HPCOOL", "J4", 1, 13, 33), ("DHWX", "J4", 2, 19, 35), ("SP-E", "J4", 3, 16, 36),
]   # rev B: the 24 VAC pair left J4 for the EXT board, so J4.1/J4.2 carry HPCOOL and DHWX
    # (SP-C and SP-D on rev A) and SP-E takes J4.3; the J8 pigtail pads are gone.
# LTV-847: channel c (1-4) has A = 2c-1, K = 2c, E = 17-2c, C = 18-2c
PI_GND = (6, 14, 20, 30, 34)       # the outer-column grounds; 9, 25 and 39 stay unconnected
GND_BUS_X = 0.75                   # pre-routed ground bus along the board edge, F.Cu
PI_5V = (2, 4)
PI_3V3 = (17,)                     # pin 1 (also 3V3) stays unconnected like the spare grounds: the
                                   # header column blocks a track between 1 and 17, and the router
                                   # otherwise reaches the link from pin 1 and strands 17's breakout
# Shadow column: one breakout pad per header row, 2.54 mm right of the inner column, carrying
# that row's odd pin where it is free, otherwise a nearby even pin. (label, Pi pin) per row 1-20;
# None leaves the row without a pad.
BREAKOUT = [None, None, ("SCL", 5, "SCL"), ("G4", 7, "GPIO4"), ("GND", 9, "GND"), ("G18", 12, "GPIO18"),
            ("SDA", 3, "SDA"), ("5V", 4, "+5V"), ("3V3", 17, "3V3"), ("G10", 19, "GPIO10"),
            ("G9", 21, "GPIO9"), ("G11", 23, "GPIO11"), ("G7", 26, "GPIO7"), ("G8", 24, "GPIO8"),
            ("GND", 30, "GND"), None, ("GND", 34, "GND"), None, ("G20", 38, "GPIO20"), ("G21", 40, "GPIO21")]
BREAKOUT_X = 4.77 + PITCH
PLUG_X = {"J1": 13.1, "J2": 24.8, "J3": 36.5, "J4": 48.2}   # pin-row centres, from the STEP
PLUG_Y = 6.95

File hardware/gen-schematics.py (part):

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                               desc="Lite-On LTV-847 quad optocoupler, DIP-16")
    S.lib("pivac:LTV-847", ltv, ltv_pins)
    S.text("pivac INT board rev B: relay-sense inputs on LTV-847 optocouplers; VS/COM arrive from the EXT board", 20, 15, 3)
    S.text("Field side (VS / COM / plugs) and Pi side (GND / GPIO) meet only inside the optocouplers.", 20, 21, 1.6)

    # channels: one row per IC, resistor + plug label per channel
    for k in (1, 2, 3):
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        hdr[p] = "+5V"
    for p in T.PI_3V3:
        hdr[p] = "3V3"
    hdr.update({3: "SDA", 5: "SCL", 7: "GPIO4"})
    for name, plug, pos, bcm, pin in T.CHANNELS:
        hdr[pin] = f"GPIO{bcm}"
    for entry in T.BREAKOUT:
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    S.text("Shadow column J9: one pad per header row (rows 1, 2, 16, 18 empty); pins 2 and 4 (5 V) carry nothing, the Pi is fed by USB-C", 250, 185, 1.6)
    S.place("Connector_Generic:Conn_01x20", "J9", "breakout", 290, 210, {i: e[2] for i, e in enumerate(T.BREAKOUT, start=1) if e},
            footprint="pivac:Shadow_1x20", hide_value=True)
    S.place("Connector_Generic:Conn_01x07", "J6", "GH link to EXT", 400, 120, dict(enumerate(("3V3", "SDA", "SCL", "GPIO4", "GND", "VS", "COM"), start=1)), footprint="Connector_JST:JST_GH_SM07B-GHS-TB_1x07-1MP_P1.25mm_Horizontal")
    for ref, net, y in (("TP1", "VS", 190), ("TP2", "COM", 200), ("TP3", "GND", 210)):
        S.place("Connector_Generic:Conn_01x01", ref, net, 400, y, {1: net}, footprint="pivac:TestPad", hide_value=True)
    S.pwr_flags(("3V3", "+5V", "GND", "VS", "COM"), 250, 270)
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    for i, (ref, io) in enumerate((("H1", "DATA"), ("H2", "DATA"), ("H3", "H3_DATA"))):
        S.place("Connector_Generic:Conn_01x03", ref, "PTSM 0,5/3-HH", 50 + i * 45, 180, {1: "VCC", 2: io, 3: "GND"}, footprint="pivac:PTSM_0.5_3-HH-2.5-THR")
    S.place("Jumper:SolderJumper_3_Open", "JP2", "H3: bus / U2", 200, 180, {1: "DATA", 2: "H3_DATA", 3: "DATA_H3"}, footprint="Jumper:SolderJumper-3_P1.3mm_Open_RoundedPad1.0x1.5mm")
    S.text("Rollback to w1-gpio: fit R1 and bridge JP1, and GPIO4 becomes the bus data line.", 20, 215, 1.6)
    S.place("Device:R", "R1", "2k2 (not fitted)", 50, 235, {1: "VCC", 2: "DATA"}, footprint="Resistor_THT:R_Axial_DIN0207_L6.3mm_D2.5mm_P10.16mm_Horizontal", dnp=True)
    S.place("Jumper:SolderJumper_2_Open", "JP1", "GPIO4 -> DATA", 90, 235, {1: "GPIO4", 2: "DATA"}, footprint="Jumper:SolderJumper-2_P1.3mm_Open_RoundedPad1.0x1.5mm")
    S.place("Connector_Generic:Conn_01x07", "J1", "GH link to INT", 250, 60, dict(enumerate(("VCC", "SDA", "SCL", "GPIO4", "GND", "VS", "COM"), start=1)), footprint="Connector_JST:JST_GH_BM07B-GHS-TBT_1x07-1MP_P1.25mm_Vertical")
    S.place("Connector_Generic:Conn_01x03", "J2", "bus pads", 250, 110, {1: "VCC", 2: "DATA", 3: "GND"}, footprint="pivac:Pads_1x3")
    # power section
    S.text("24 VAC in on J3, PTC F1, bridge D1-D4, C3 470 uF: VS about 35 V DC against COM, out to INT on J1.6/J1.7 and into U3.", 20, 270, 1.6)
    S.text("U3 makes 5.1 V isolated for the Pi: C4 at its output, J4 to a USB-C pigtail. Remote (pin 3) open = on. COM never meets GND.", 20, 276, 1.6)
    S.place("Connector_Generic:Conn_01x02", "J3", "PTSM 0,5/2-HH 24 VAC", 40, 300, {1: "ACR", 2: "ACC"}, footprint="pivac:PTSM_0.5_2-HH-2.5-THR")
    S.place("Device:Fuse", "F1", "PTC 1.1A 60V", 80, 300, {1: "ACR", 2: "ACF"}, footprint="pivac:PTC_Radial_P5.08_Standing")
    for ref, a, kk, x in (("D1", "ACF", "VS", 120), ("D2", "ACC", "VS", 140), ("D3", "COM", "ACF", 160), ("D4", "COM", "ACC", 180)):
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    S.text("Probe sockets PTSM 0,5/3-HH-2,5-SMD: 1 VCC, 2 DATA, 3 GND. H1 is the trunk, H2 a spare on the same bus.", 20, 160, 1.6)
    for i, ref in enumerate(("H1", "H2")):
        S.place("Connector_Generic:Conn_01x03", ref, "PTSM 0,5/3-HH-SMD", 50 + i * 45, 180, {1: "VCC", 2: "DATA", 3: "GND"}, footprint="pivac:PTSM_0.5_3-HH-2.5-SMD")
    S.text("Rollback to w1-gpio: fit R1 and bridge JP1, and GPIO4 becomes the bus data line.", 20, 215, 1.6)
    S.place("Device:R", "R1", "2k2 (not fitted)", 50, 235, {1: "VCC", 2: "DATA"}, footprint="Resistor_THT:R_Axial_DIN0207_L6.3mm_D2.5mm_P10.16mm_Horizontal", dnp=True)
    S.place("Jumper:SolderJumper_2_Open", "JP1", "GPIO4 -> DATA", 90, 235, {1: "GPIO4", 2: "DATA"}, footprint="Jumper:SolderJumper-2_P1.3mm_Open_RoundedPad1.0x1.5mm")
    S.place("Connector_Generic:Conn_01x07", "J1", "GH link to INT", 250, 60, dict(enumerate(("VCC", "SDA", "SCL", "GPIO4", "GND", "VS", "COM"), start=1)), footprint="Connector_JST:JST_GH_BM07B-GHS-TBT_1x07-1MP_P1.25mm_Vertical")
    S.place("Connector_Generic:Conn_01x03", "J2", "bus pads", 250, 110, {1: "VCC", 2: "DATA", 3: "GND"}, footprint="pivac:Pads_1x3")
    S.text("24VAC input on J3 (1 = R, 2 = C), PTC F1 in the R leg, bridge D1-D4, C3 470 uF: VS about 35 V DC against COM, out to INT on J1.6/J1.7 and into U3.", 20, 270, 1.6)
    S.text("U3 makes 5.1 V isolated for the Pi: C4 at its output, J4 (1 = +5 V, 2 = GND) to a USB-C pigtail. J3 is black and J4 white: they take the same plug.", 20, 276, 1.6)
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                                 desc="Lite-On LTV-814S AC-input optocoupler, SMD-4")
    S.lib("pivac:LTV-814S", opto, opto_pins)
    S.text("pivac air-handler node shield for the UNO R4 WiFi (docs/air-handler-shield-pcb-plan.md)", 20, 15, 3)
    S.text("24 VAC on TB1 (R, C, Y2, W2). F1, D2 TVS, D1 half-wave into C1: VS about 35 V against C (net COM). U1 isolates and feeds the R4's 5V pin.", 20, 21, 1.6)
    S.place("Connector_Generic:Conn_01x04", "TB1", "MC 1,5/4-G-3,81 24VAC", 30, 50, {4: "ACR", 3: "COM", 2: "Y2", 1: "W2"}, footprint="Connector_Phoenix_MC:PhoenixContact_MC_1,5_4-G-3.81_1x04_P3.81mm_Horizontal")
    S.place("Device:Fuse", "F1", "1812L020/60DR", 60, 50, {2: "ACR", 1: "ACF"}, footprint="Fuse:Fuse_1812_4532Metric_Pad1.30x3.40mm_HandSolder")
    S.place("Device:D_TVS", "D2", "SMAJ43CA", 85, 50, {1: "ACF", 2: "COM"}, footprint="Diode_SMD:D_SMA")
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        S.place("Device:LED", led, col, 80, y, {2: b, 1: c}, footprint="LED_SMD:LED_0805_2012Metric_Pad1.15x1.40mm_HandSolder")
        S.place("Device:D", dap, "1N4148W", 105, y, {1: b, 2: c}, footprint="Diode_SMD:D_SOD-123")
        S.place("Device:R", rsh, "1k", 130, y, {1: c, 2: "COM"}, footprint="Resistor_SMD:R_0805_2012Metric_Pad1.20x1.40mm_HandSolder")
        S.place("pivac:LTV-814S", opt, "LTV-814S", 165, y, {1: c, 2: "COM", 3: "GND", 4: pin}, footprint="Package_DIP:SMDIP-4_W9.53mm")
        S.place("Device:R", rpu, "10k", 200, y, {1: pin, 2: "+5V"}, footprint="Resistor_SMD:R_0805_2012Metric_Pad1.20x1.40mm_HandSolder")
        S.place("Device:C", cf, "1u", 220, y, {1: pin, 2: "GND"}, footprint="Capacitor_SMD:C_0805_2012Metric_Pad1.18x1.45mm_HandSolder")
    S.text("Air temperatures: 10.0k 0.1% from 5 V to each NTC on TB2, 1k to A0 and A1, 100n at the pins.", 20, 200, 1.6)
    S.place("Connector_Generic:Conn_01x04", "TB2", "PTSM 0,5/4-HH-2,5-SMD air", 30, 220, {1: "AIRS", 2: "GND", 3: "AIRR", 4: "GND"}, footprint="pivac:PTSM_0.5_4-HH-2.5-SMD")
    for j, (rd, rs, cc, node, pin) in enumerate((("R1", "R3", "C5", "AIRR", "A0"), ("R2", "R4", "C6", "AIRS", "A1"))):
        x = 70 + j * 70
        S.place("Device:R", rd, "10k0 0.1%", x, 220, {1: "+5V", 2: node}, footprint="Resistor_SMD:R_0805_2012Metric_Pad1.20x1.40mm_HandSolder")
        S.place("Device:R", rs, "1k", x + 20, 220, {1: node, 2: pin}, footprint="Resistor_SMD:R_0805_2012Metric_Pad1.20x1.40mm_HandSolder")
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
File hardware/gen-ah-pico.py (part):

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    B.text(lab, LX + 5.6, y, layer="B.SilkS", size=0.7, bold=True)

# --- USB lockout (plan §0, Rev C), on the back: a laptop on the micro-USB cuts U1 off the Pico and J4 off its data
# Q1 and R11 behind the Pico's VBUS and VSYS pins; U5 under the Pico, straight below TP2 and TP3 between the
# Pico's USB leg holes, its common pins up toward them and its HSD1 pins down, from where J4 is routed
B.lib("Q1", "Package_TO_SOT_SMD", "SOT-23_Handsoldering", 42.6, 5.2, 0, back=True, value="DMG2305UX-7")
B.lib("R11", *R_0805, 40.6, 9.3, 90, back=True, value="100k")
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    x, y = u(n)
    net = B.refs["U5"].FindPadByNumber(str(n)).GetNetname()
    path(net, "B.Cu", (x, y), (x, y + reach), width=0.2)
path("ACR", "F.Cu", pj1, (47.8, 11.2), f1a)
path("ACF", "F.Cu", f1b, (52.6, d2a[1]), d2a)
path("ACF", "F.Cu", f1b, (49.4, 16.4)); via("ACF", 49.4, 16.4)
path("ACF", "B.Cu", (49.4, 16.4), (49.0, 17.0), (49.0, 26.0), (55.7, 33.0), (55.7, 35.6)); via("ACF", 55.7, 35.6)
path("ACF", "F.Cu", (55.7, 35.6), d1a)
path("VS", "F.Cu", u1v, (50.5, u1v[1]), d1v); path("VS", "F.Cu", (51.2, u1v[1]), (50.5, u1v[1])); path("VS", "F.Cu", (51.2, u1v[1]), c1v)
path("COM", "B.Cu", u1c, (45.9, u1c[1]), (47.5, 35.4), (47.5, 12.0), pj2)
path("COM", "B.Cu", (47.5, 12.0), (52.9, 12.0), (52.9, d2c[1])); via("COM", 52.9, d2c[1])
path("COM", "F.Cu", (52.9, d2c[1]), d2c)
path("COM", "F.Cu", c1c, (47.5, c1c[1])); via("COM", 47.5, c1c[1])
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

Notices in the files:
README.md:
Licensing:
pivac is free for personal and other noncommercial use. Commercial use, including installing it for a customer, building it into a product, or selling boards made from these designs, needs a separate licence from the copyright holder; ask through [github.com/dglcinc](https://github.com/dglcinc).
Content | Licence
Code, scripts, firmware, configuration | PolyForm Noncommercial 1.0.0 (`LICENSE`)
Documents, drawings, images, board designs | CC BY-NC 4.0 (`LICENSE-DOCS`)
`hardware/vendor/` | Each maker's own terms
1. The code row covers `pivac/`, `scripts
